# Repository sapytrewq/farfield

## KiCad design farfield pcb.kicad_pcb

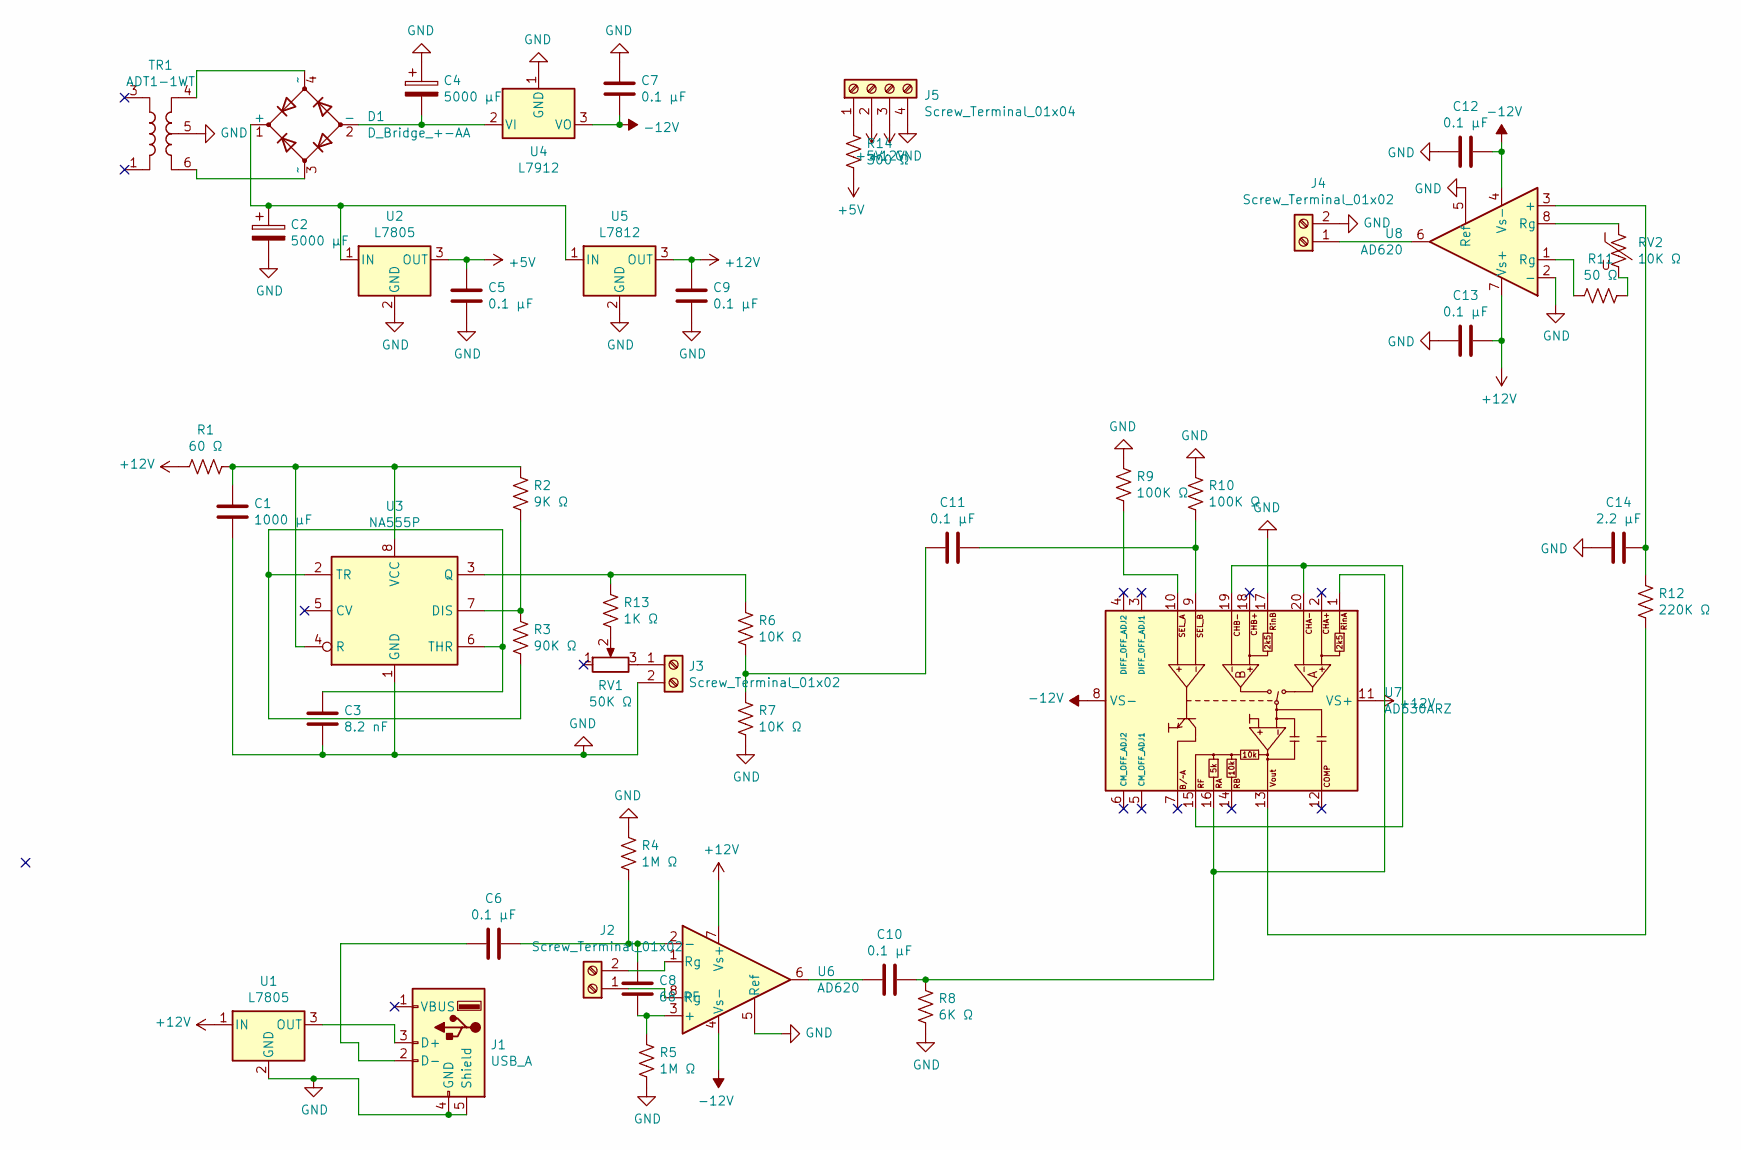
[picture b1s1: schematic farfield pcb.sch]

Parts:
C1: 1000 μF; CP_Radial_D10.0mm_P5.00mm
C2, C4: 5000 μF; CP_Radial_D16.0mm_P7.50mm
C3: 8.2 nF; C_Disc_D4.7mm_W2.5mm_P5.00mm
C5, C6, C7, C9, C10, C11, C12, C13: 0.1 μF; C_Disc_D3.8mm_W2.6mm_P2.50mm
C8: 68 PF; C_Disc_D3.8mm_W2.6mm_P2.50mm
C14: 2.2 μF; C_Disc_D4.7mm_W2.5mm_P5.00mm
D1: D_Bridge_+-AA; DIP-4_W7.62mm
J1: USB_A; USB_A_Molex_105057_Vertical
J2, J3, J4: Screw_Terminal_01x02; TerminalBlock_Phoenix_MKDS-3-2-5.08_1x02_P5.08mm_Horizontal
J5: Screw_Terminal_01x04; TerminalBlock_Phoenix_MKDS-3-4-5.08_1x04_P5.08mm_Horizontal
R1: 60 Ω; R_Axial_DIN0207_L6.3mm_D2.5mm_P7.62mm_Horizontal
R2: 9K Ω; R_Axial_DIN0207_L6.3mm_D2.5mm_P7.62mm_Horizontal
R3: 90K Ω; R_Axial_DIN0207_L6.3mm_D2.5mm_P7.62mm_Horizontal
R4, R5: 1M Ω; R_Axial_DIN0204_L3.6mm_D1.6mm_P5.08mm_Horizontal
R6, R7: 10K Ω; R_Axial_DIN0207_L6.3mm_D2.5mm_P7.62mm_Horizontal
R8: 6K Ω; R_Axial_DIN0207_L6.3mm_D2.5mm_P7.62mm_Horizontal
R9, R10: 100K Ω; R_Axial_DIN0207_L6.3mm_D2.5mm_P7.62mm_Horizontal
R11: 50 Ω; R_Axial_DIN0207_L6.3mm_D2.5mm_P7.62mm_Horizontal
R12: 220K Ω; R_Axial_DIN0207_L6.3mm_D2.5mm_P7.62mm_Horizontal
R13: 1K Ω; R_Axial_DIN0207_L6.3mm_D2.5mm_P7.62mm_Horizontal
R14: 300 Ω; R_Axial_DIN0207_L6.3mm_D2.5mm_P7.62mm_Horizontal
RV1: 50K Ω; Potentiometer_Bourns_3266Y_Vertical
RV2: 10K Ω; Potentiometer_Bourns_3266Y_Vertical
TR1: ADT1-1WT; TerminalBlock_Phoenix_MKDS-3-6-5.08_1x06_P5.08mm_Horizontal
U1, U2: L7805; TO-220-3_Vertical
U3: NA555P; DIP-8_W7.62mm
U4: L7912; TO-220-3_Vertical
U5: L7812; TO-220-3_Vertical
U6, U8: AD620; DIP-8_W7.62mm
U7: AD630ARZ; DIP-20_W7.62mm

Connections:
+5V: C5.1, J5.2, R14.2, U2.3 (OUT)
+12V: C9.1, C13.1, J5.3, R1.2, U1.1 (IN), U5.3 (OUT), U6.7 (Vs+), U7.11 (VS+), U8.7 (Vs+)
-12V: C7.1, C12.1, U4.3 (VO), U6.4 (Vs-), U7.8 (VS-), U8.4 (Vs-)
unnamed: C1.1, R1.1, R2.1, U3.4 (R), U3.8 (VCC)
unnamed: C2.1, D1.1 (+), U2.1 (IN), U5.1 (IN)
unnamed: C3.1, R3.2, U3.2 (TR), U3.6 (THR)
unnamed: C4.2, D1.2 (-), U4.2 (VI)
unnamed: C6.1, J1.2 (D-)
unnamed: C6.2, C8.1, R4.2, U6.2 (-)
unnamed: C8.2, R5.1, U6.3 (+)
unnamed: C10.1, R8.1, U7.1 (RinA), U7.16 (RA)
unnamed: C10.2, U6.6
unnamed: C11.1, R10.2, U7.9 (SEL_B)
unnamed: C11.2, R6.2, R7.1
unnamed: C14.1, R12.1, U8.3 (+)
unnamed: D1.3 (~~), TR1.6
unnamed: D1.4 (~~), TR1.4
unnamed: J1.3 (D+), U1.3 (OUT)
unnamed: J2.1, U6.8 (Rg)
unnamed: J2.2, U6.1 (Rg)
unnamed: J3.1, RV1.3
unnamed: J4.1, U8.6
unnamed: J5.1, R14.1
unnamed: R2.2, R3.1, U3.7 (DIS)
unnamed: R9.1, U7.10 (SEL_A)
unnamed: R11.1, RV2.2
unnamed: R11.2, U8.1 (Rg)
unnamed: R12.2, U7.13 (Vout)
unnamed: R6.1, R13.1, U3.3 (Q)
unnamed: R13.2, RV1.2
unnamed: RV2.1, U8.8 (Rg)
unnamed: U7.15 (RF), U7.19 (CHB-), U7.20 (CHA-)

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
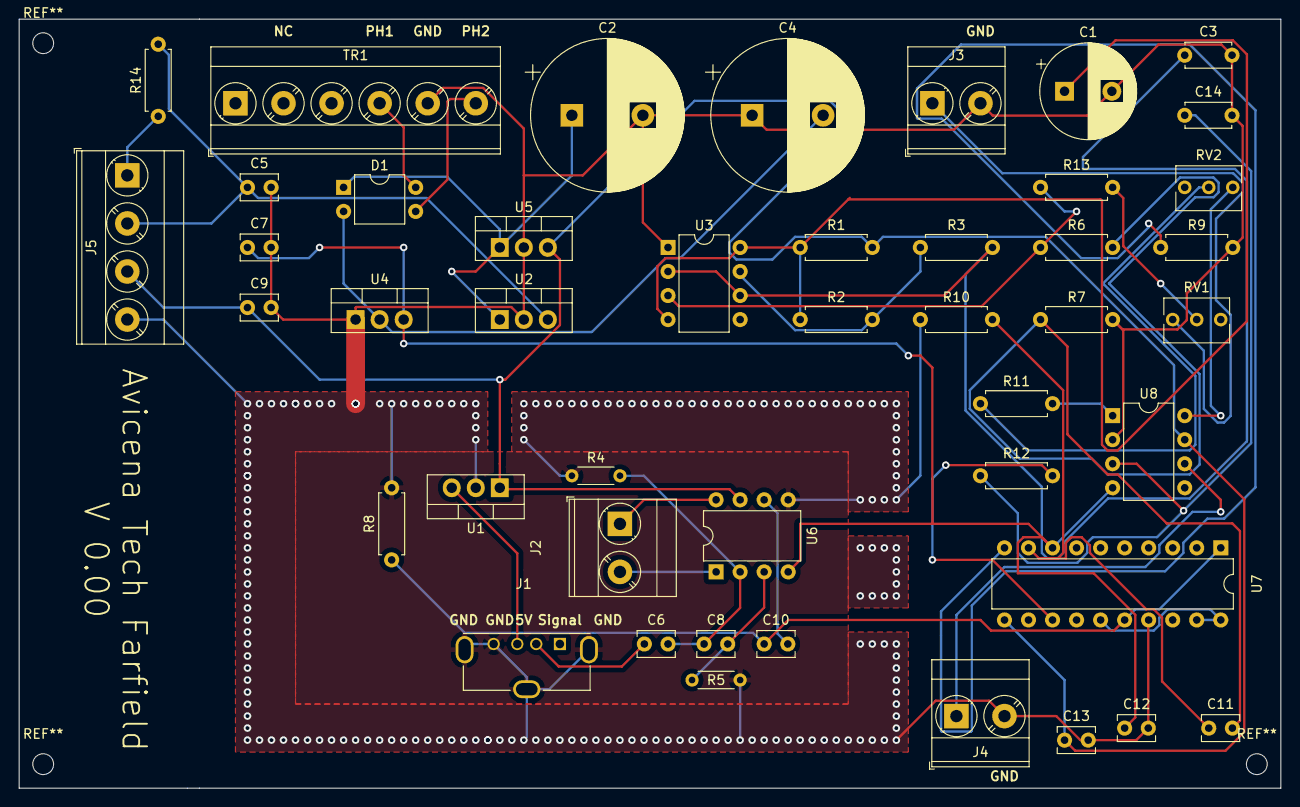
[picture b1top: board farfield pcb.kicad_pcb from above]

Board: 2 copper layers, 133.3 x 81.3 mm, 45 parts (0 on the bottom side), 33 nets.

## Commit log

2020-06-30 fully working servo control
2020-07-21 finikshed code
2020-07-23 updated 3d graphing utilities
2020-07-23 updated two-dimensional plots with directivity
2020-07-23 debugged and working
2020-07-24 fixed plotting
2020-07-24 updated mayavi lighting
2020-07-24 added pretty mesh plotting
2020-07-28 Add files via upload
    KiCAD PCB Files
2020-07-28 Add files via upload
    CAD Files
2020-07-28 Gain setting added
2020-07-28 added armpositioning
2020-07-30 Updated Graphing
2020-07-31 graphing utility added
2020-07-31 testing branch
2020-07-31 updated graphing utlity
2020-07-31 Mayavi Graphing
2020-08-07 skewed thing fixed
2021-04-27 updated scripts
2021-07-23 constant gain
2021-07-26 Text apperas when constant gain is set
2021-07-27 7-26 data
